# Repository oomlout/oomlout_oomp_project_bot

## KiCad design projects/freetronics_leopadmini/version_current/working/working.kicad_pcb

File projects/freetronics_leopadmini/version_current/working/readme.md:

# LEOPADMINI by freetronics  
This is a harvested standardized copy of a project from github.  
The original project can be found at:  
https://github.com/freetronics/LEOPADMINI  
Please consult that link for additional, details, files, and license information.  
Note: It was auto harvested and if the original repo had more than one board file or anything out of the ordinary the files here are likely not representative.

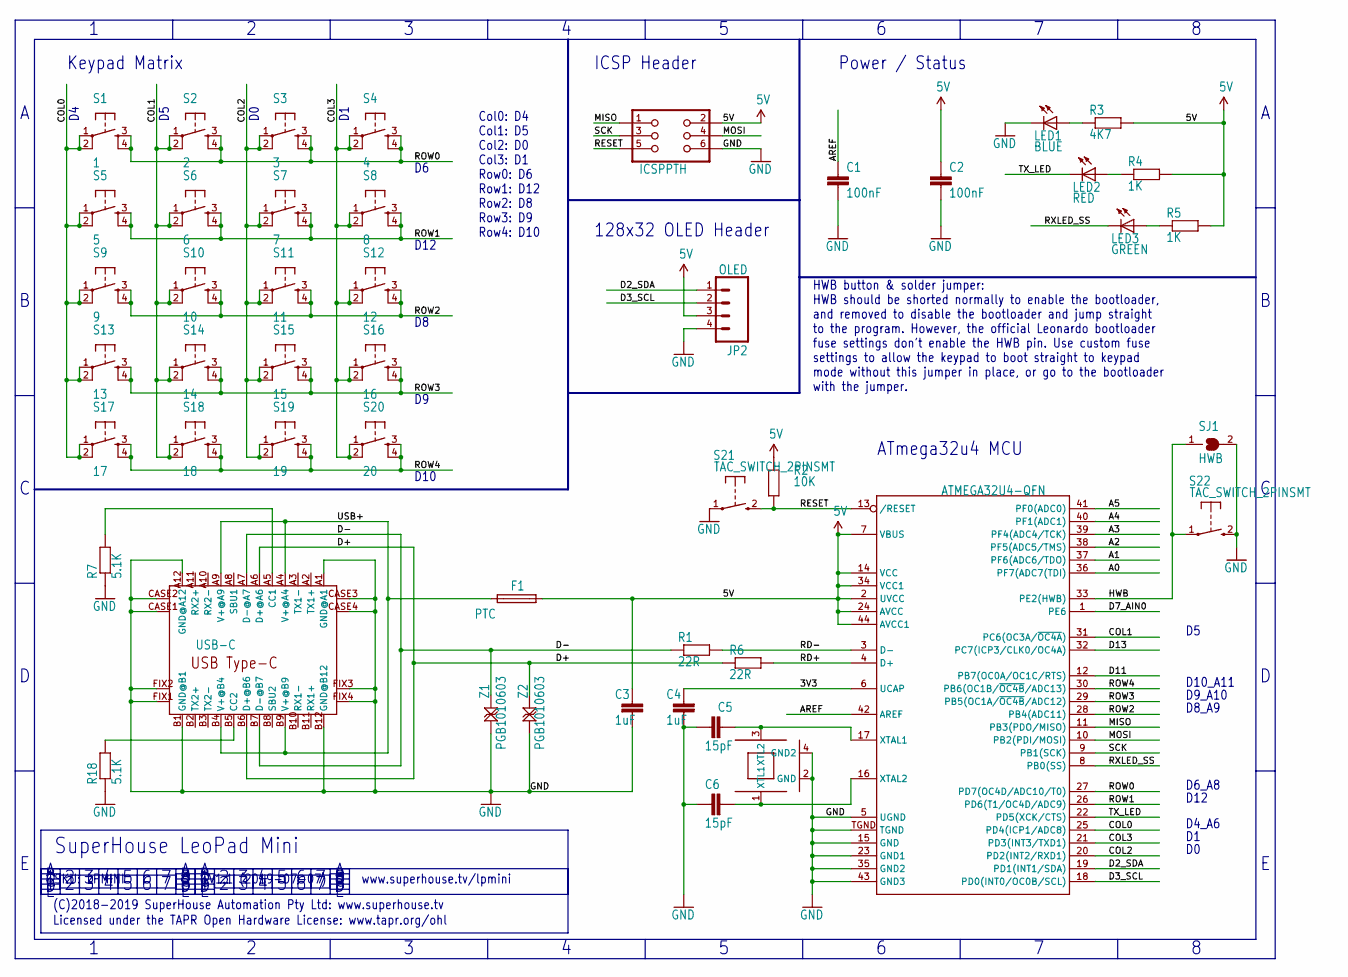
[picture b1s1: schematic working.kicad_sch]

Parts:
C1, C2: 100nF; C0603
C3, C4: 1uF; C0603
C5, C6: 15pF; C0603
F1: PTC; 1812
IC1: ATMEGA32U4-QFN; QFN-44N
ICSP0: ICSPPTH; 2X03PTH
JP2: OLED; 1X04
LED1: BLUE; LED-0603
LED2: RED; LED-0603
LED3: GREEN; LED-0603
R1, R6: 22R; R0603
R2: 10K; R0603
R3: 4K7; R0603
R4, R5: 1K; R0603
R7, R18: 5.1K; R0603
S1: 1; TACTILE-PTH-6MM
S2: 2; TACTILE-PTH-6MM
S3: 3; TACTILE-PTH-6MM
S4: 4; TACTILE-PTH-6MM
S5: 5; TACTILE-PTH-6MM
S6: 6; TACTILE-PTH-6MM
S7: 7; TACTILE-PTH-6MM
S8: 8; TACTILE-PTH-6MM
S9: 9; TACTILE-PTH-6MM
S10: 10; TACTILE-PTH-6MM
S11: 11; TACTILE-PTH-6MM
S12: 12; TACTILE-PTH-6MM
S13: 13; TACTILE-PTH-6MM
S14: 14; TACTILE-PTH-6MM
S15: 15; TACTILE-PTH-6MM
S16: 16; TACTILE-PTH-6MM
S17: 17; TACTILE-PTH-6MM
S18: 18; TACTILE-PTH-6MM
S19: 19; TACTILE-PTH-6MM
S20: 20; TACTILE-PTH-6MM
S21, S22: TAC_SWITCH_2PINSMT; TACTILE_SMD_3X4X2
SJ1: HWB; SJ
U$15: USB-C; USB-C-U52A
XTL1: CRYSTAL-GND3X2; CRYSTAL-SMD-3X2
Z1, Z2: PGB1010603; TVS0603

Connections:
3V3: C4.2, IC1.6 (UCAP)
5V: C2.1, C3.1, F1.2, IC1.2 (UVCC), IC1.7 (VBUS), IC1.14 (VCC), IC1.24 (AVCC), IC1.34 (VCC1), IC1.44 (AVCC1), ICSP0.2, JP2.3, R2.2, R3.2, R4.2, R5.2
A0: IC1.36 (PF7(ADC7(TDI))
A1: IC1.37 (PF6(ADC6/TDO))
A2: IC1.38 (PF5(ADC5/TMS))
A3: IC1.39 (PF4(ADC4/TCK))
A4: IC1.40 (PF1(ADC1))
A5: IC1.41 (PF0(ADC0))
AREF: C1.1, IC1.42 (AREF)
COL0: IC1.25 (PD4(ICP1/ADC8)), S1.1, S1.2, S5.1, S5.2, S9.1, S9.2, S13.1, S13.2, S17.1, S17.2
COL1: IC1.31 (PC6(OC3A/~OC4A)), S2.1, S2.2, S6.1, S6.2, S10.1, S10.2, S14.1, S14.2, S18.1, S18.2
COL2: IC1.20 (PD2(INT2/RXD1)), S3.1, S3.2, S7.1, S7.2, S11.1, S11.2, S15.1, S15.2, S19.1, S19.2
COL3: IC1.21 (PD3(INT3/TXD1)), S4.1, S4.2, S8.1, S8.2, S12.1, S12.2, S16.1, S16.2, S20.1, S20.2
D2_SDA: IC1.19 (PD1(INT1/SDA)), JP2.1
D3_SCL: IC1.18 (PD0(INT0/OC0B/SCL)), JP2.2
D7_AIN0: IC1.1 (PE6)
D11: IC1.12 (PB7(OC0A/OC1C/RTS))
D13: IC1.32 (PC7(ICP3/CLK0/OC4A))
D+: R6.1, U$15.A6 (D+@A6), U$15.B6 (D+@B6), Z2.2
D-: R1.1, U$15.A7 (D-@A7), U$15.B7 (D-@B7), Z1.2
GND: C1.2, C2.2, C3.2, C4.1, C5.1, C6.1, IC1.5 (UGND), IC1.15 (GND), IC1.23 (GND1), IC1.35 (GND2), IC1.43 (GND3), IC1.TGND, ICSP0.6, JP2.4, LED1.C, R7.1, R18.1, S21.1, S22.2 (S), SJ1.2, U$15.A1 (GND@A1), U$15.A12 (GND@A12), U$15.B1 (GND@B1), U$15.B12 (GND@B12), U$15.CASE1 (GND@CASE1), U$15.CASE2 (GND@CASE2), U$15.CASE3 (GND@CASE3), U$15.CASE4 (GND@CASE4), U$15.FIX1 (GND@FIX1), U$15.FIX2 (GND@FIX2), U$15.FIX3 (GND@FIX3), U$15.FIX4 (GND@FIX4), XTL1.2 (GND), XTL1.4 (GND2), Z1.1, Z2.1
HWB: IC1.33 (PE2(HWB)), S22.1, SJ1.1
MISO: IC1.11 (PB3(PDO/MISO)), ICSP0.1
MOSI: IC1.10 (PB2(PDI/MOSI)), ICSP0.4
unnamed: R18.2, U$15.B5 (CC2)
unnamed: LED1.A, R3.1
unnamed: LED2.A, R4.1
unnamed: LED3.A, R5.1
unnamed: C5.2, IC1.17 (XTAL1), XTL1.3 (XTL2)
unnamed: C6.2, IC1.16 (XTAL2), XTL1.1 (XTL1)
unnamed: R7.2, U$15.A5 (CC1)
RD+: IC1.4 (D+), R6.2
RD-: IC1.3 (D-), R1.2
RESET: IC1.13 (/RESET), ICSP0.5, R2.1, S21.2 (S)
ROW0: IC1.27 (PD7(OC4D/ADC10/T0)), S1.3, S1.4, S2.3, S2.4, S3.3, S3.4, S4.3, S4.4
ROW1: IC1.26 (PD6(T1/OC4D/ADC9)), S5.3, S5.4, S6.3, S6.4, S7.3, S7.4, S8.3, S8.4
ROW2: IC1.28 (PB4(ADC11)), S9.3, S9.4, S10.3, S10.4, S11.3, S11.4, S12.3, S12.4
ROW3: IC1.29 (PB5(OC1A/~OC4B/ADC12)), S13.3, S13.4, S14.3, S14.4, S15.3, S15.4, S16.3, S16.4
ROW4: IC1.30 (PB6(OC1B/~OC4B/ADC13)), S17.3, S17.4, S18.3, S18.4, S19.3, S19.4, S20.3, S20.4
RXLED_SS: IC1.8 (PB0(SS)), LED3.C
SCK: IC1.9 (PB1(SCK)), ICSP0.3
TX_LED: IC1.22 (PD5(XCK/CTS)), LED2.C
USB+: F1.1, U$15.A4 (V+@A4), U$15.A9 (V+@A9), U$15.B4 (V+@B4), U$15.B9 (V+@B9)

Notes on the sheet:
Col0: D4 Col1: D5 Col2: D0 Col3: D1 Row0: D6 Row1: D12 Row2: D8 Row3: D9 Row4: D10
D12
128x32 OLED Header
D9_A10
D6_A8
V1.1 (2019-07-07)
D10
(C)2018-2019 SuperHouse Automation Pty Ltd: www.superhouse.tv
Keypad Matrix
HWB button & solder jumper: HWB should be shorted normally to enable the bootloader, and removed to disable the bootloader and jump straight to the program. However, the official Leonardo bootloader fuse settings don't enable the HWB pin. Use custom fuse settings to allow the keypad to boot straigh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
Licensed under the TAPR Open Hardware License: www.tapr.org/ohl
D4_A6
SuperHouse LeoPad Mini
ICSP Header
Power / Status
D10_A11
SKU: LPMINI
D8_A9
www.superhouse.tv/lpmini
ATmega32u4 MCU

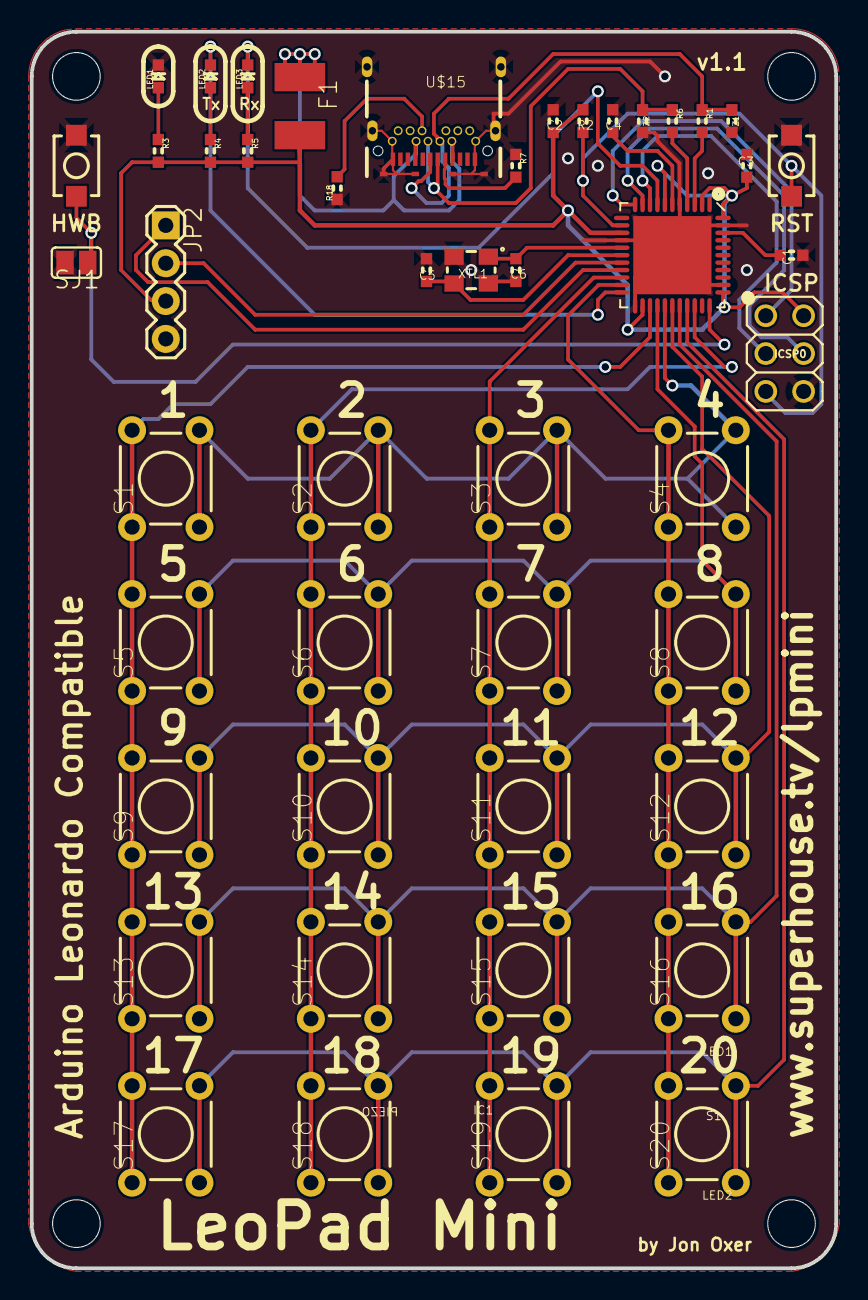
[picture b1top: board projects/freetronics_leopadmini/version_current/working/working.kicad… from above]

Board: 2 copper layers, 54.0 x 83.0 mm, 52 parts (0 on the bottom side), 34 nets.

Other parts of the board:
@HOLE0, @HOLE1, @HOLE2, @HOLE3: (no value)

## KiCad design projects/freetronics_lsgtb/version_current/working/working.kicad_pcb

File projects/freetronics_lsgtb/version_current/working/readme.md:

# LSGTB by freetronics  
This is a harvested standardized copy of a project from github.  
The original project can be found at:  
https://github.com/freetronics/LSGTB  
Please consult that link for additional, details, files, and license information.  
Note: It was auto harvested and if the original repo had more than one board file or anything out of the ordinary the files here are likely not representative.

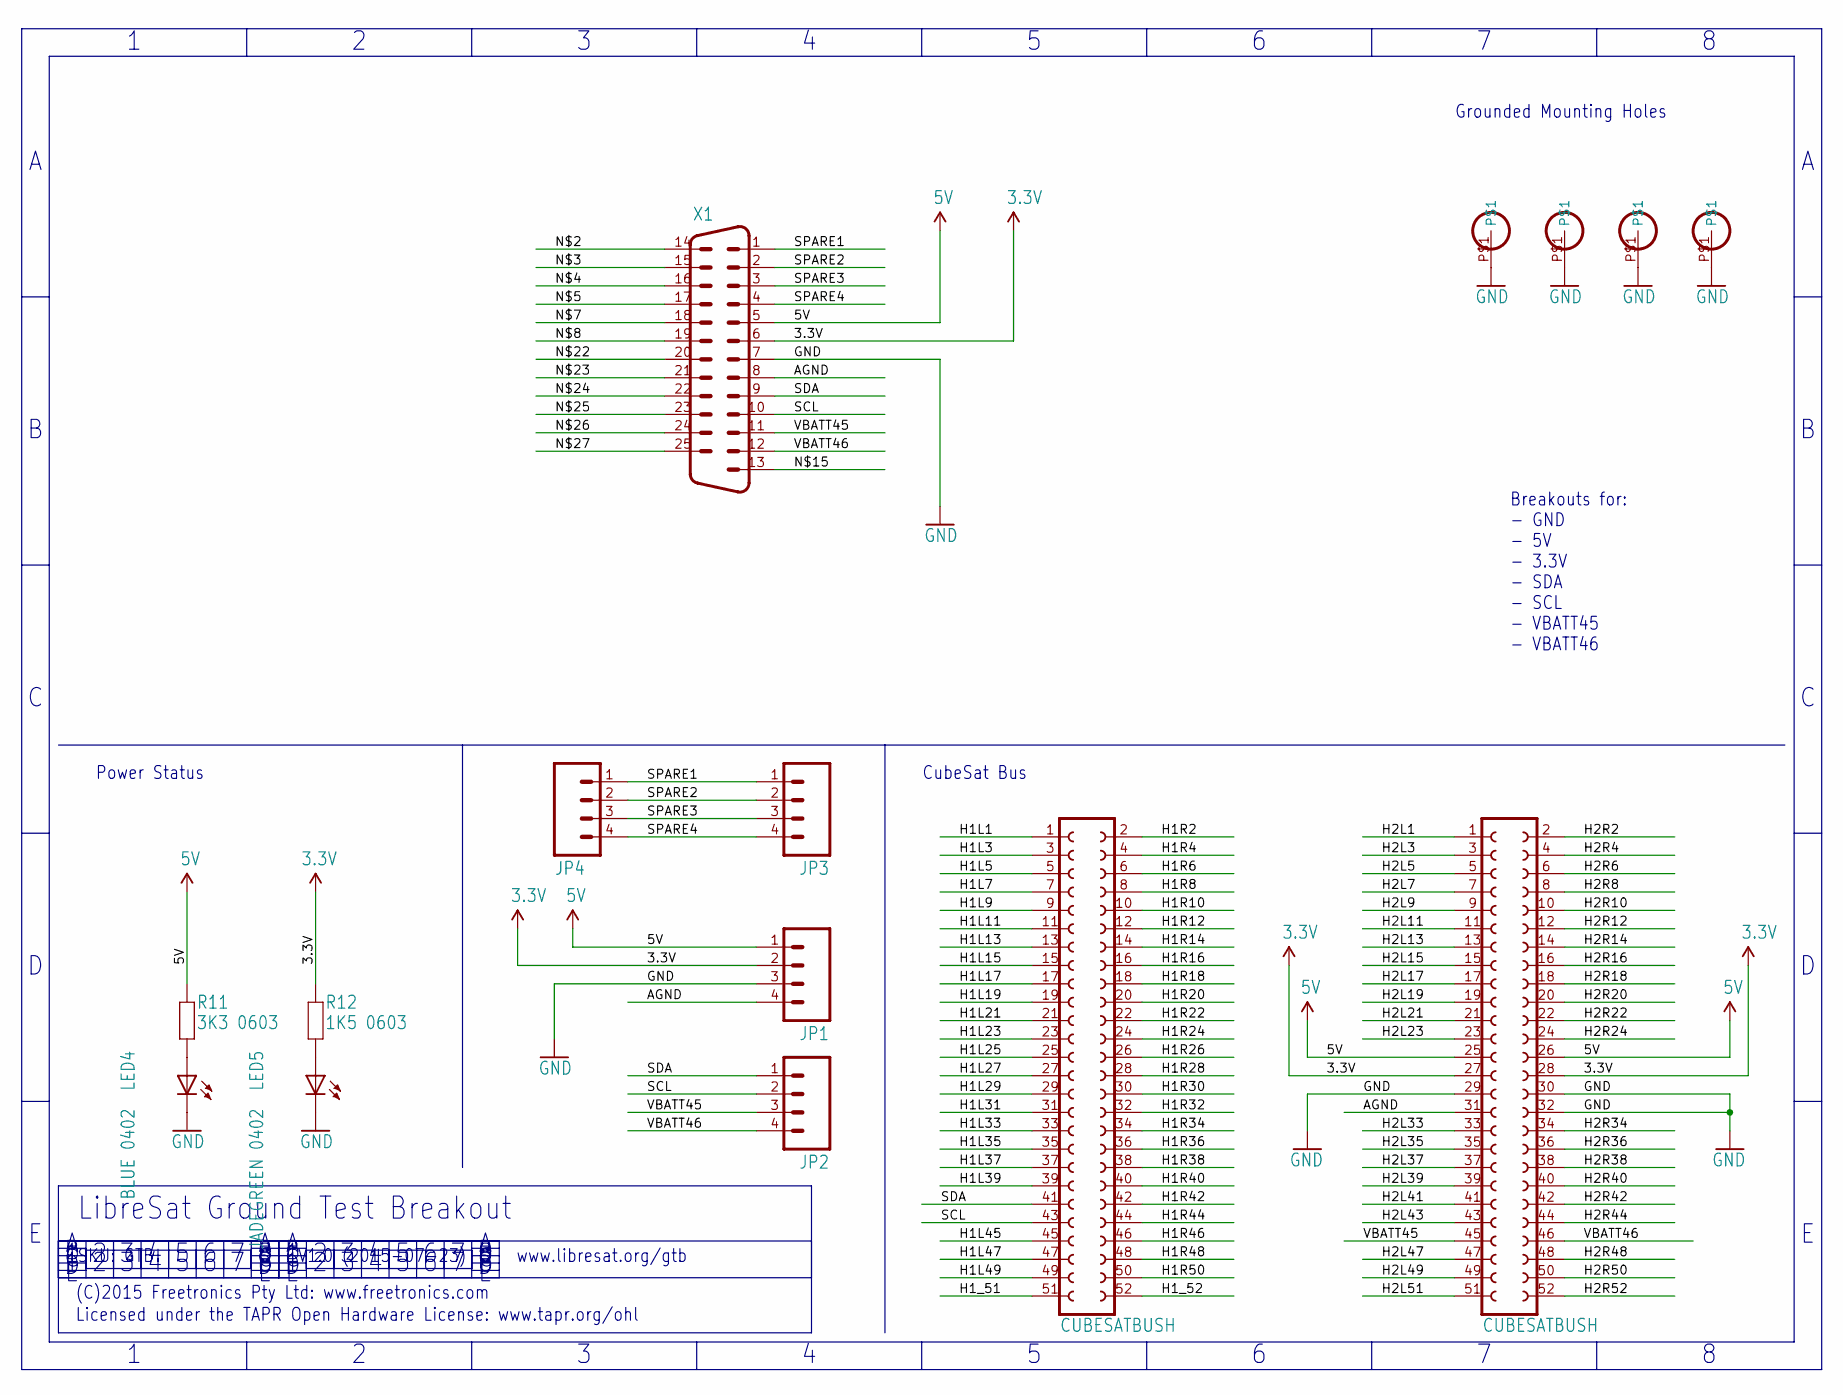
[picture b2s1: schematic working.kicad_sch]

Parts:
H1, H2: CUBESATBUSH; CUBESATBUS
JP1, JP2, JP3: M04SCREW; SCREWTERMINAL-3.5MM-4
JP4: M04PTH; 1X04
LED4: BLUE 0402; LED-0603
LED5: JADEGREEN 0402; LED-0603
MNT1, MNT2, MNT3, MNT4: HOLE3.2MM; HOLE32
R11: 3K3 0603; 0603
R12: 1K5 0603; 0603
X1: DB25HP; M25HP

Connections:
3.3V: H2.27, H2.28, JP1.2, R12.1, X1.6
5V: H2.25, H2.26, JP1.1, R11.1, X1.5
AGND: H2.31, JP1.4, X1.8
GND: H2.29, H2.30, H2.32, JP1.3, LED4.C, LED5.C, MNT1.P$1, MNT2.P$1, MNT3.P$1, MNT4.P$1, X1.7
H1L1: H1.1
H1L3: H1.3
H1L5: H1.5
H1L7: H1.7
H1L9: H1.9
H1L11: H1.11
H1L13: H1.13
H1L15: H1.15
H1L17: H1.17
H1L19: H1.19
H1L21: H1.21
H1L23: H1.23
H1L25: H1.25
H1L27: H1.27
H1L29: H1.29
H1L31: H1.31
H1L33: H1.33
H1L35: H1.35
H1L37: H1.37
H1L39: H1.39
H1L45: H1.45
H1L47: H1.47
H1L49: H1.49
H1R2: H1.2
H1R4: H1.4
H1R6: H1.6
H1R8: H1.8
H1R10: H1.10
H1R12: H1.12
H1R14: H1.14
H1R16: H1.16
H1R18: H1.18
H1R20: H1.20
H1R22: H1.22
H1R24: H1.24
H1R26: H1.26
H1R28: H1.28
H1R30: H1.30
H1R32: H1.32
H1R34: H1.34
H1R36: H1.36
H1R38: H1.38
H1R40: H1.40
H1R42: H1.42
H1R44: H1.44
H1R46: H1.46
H1R48: H1.48
H1R50: H1.50
H1_51: H1.51
H1_52: H1.52
H2L1: H2.1
H2L3: H2.3
H2L5: H2.5
H2L7: H2.7
H2L9: H2.9
H2L11: H2.11
H2L13: H2.13
H2L15: H2.15
H2L17: H2.17
H2L19: H2.19
H2L21: H2.21
H2L23: H2.23
H2L33: H2.33
H2L35: H2.35
H2L37: H2.37
H2L39: H2.39
H2L41: H2.41
H2L43: H2.43
H2L47: H2.47
H2L49: H2.49
H2L51: H2.51
H2R2: H2.2
H2R4: H2.4
H2R6: H2.6
H2R8: H2.8
H2R10: H2.10
H2R12: H2.12
H2R14: H2.14
H2R16: H2.16
H2R18: H2.18
H2R20: H2.20
H2R22: H2.22
H2R24: H2.24
H2R34: H2.34
H2R36: H2.36
H2R38: H2.38
H2R40: H2.40
H2R42: H2.42
H2R44: H2.44
H2R48: H2.48
H2R50: H2.50
H2R52: H2.52
unnamed: LED5.A, R12.2
unnamed: LED4.A, R11.2
SCL: H1.43, JP2.2, X1.10
SDA: H1.41, JP2.1, X1.9
SPARE1: JP3.1, JP4.1, X1.1
SPARE2: JP3.2, JP4.2, X1.2
SPARE3: JP3.3, JP4.3, X1.3
SPARE4: JP3.4, JP4.4, X1.4
VBATT45: H2.45, JP2.3, X1.11
VBATT46: H2.46, JP2.4, X1.12

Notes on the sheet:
(C)2015 Freetronics Pty Ltd: www.freetronics.com
V1.0 (2015-07-23)
Licensed under the TAPR Open Hardware License: www.tapr.org/ohl
Breakouts for: - GND - 5V - 3.3V - SDA - SCL - VBATT45 - VBATT46
Grounded Mounting Holes
CubeSat Bus
www.libresat.org/gtb
SKU: GTB
LibreSat Ground Test Breakout
Power Status

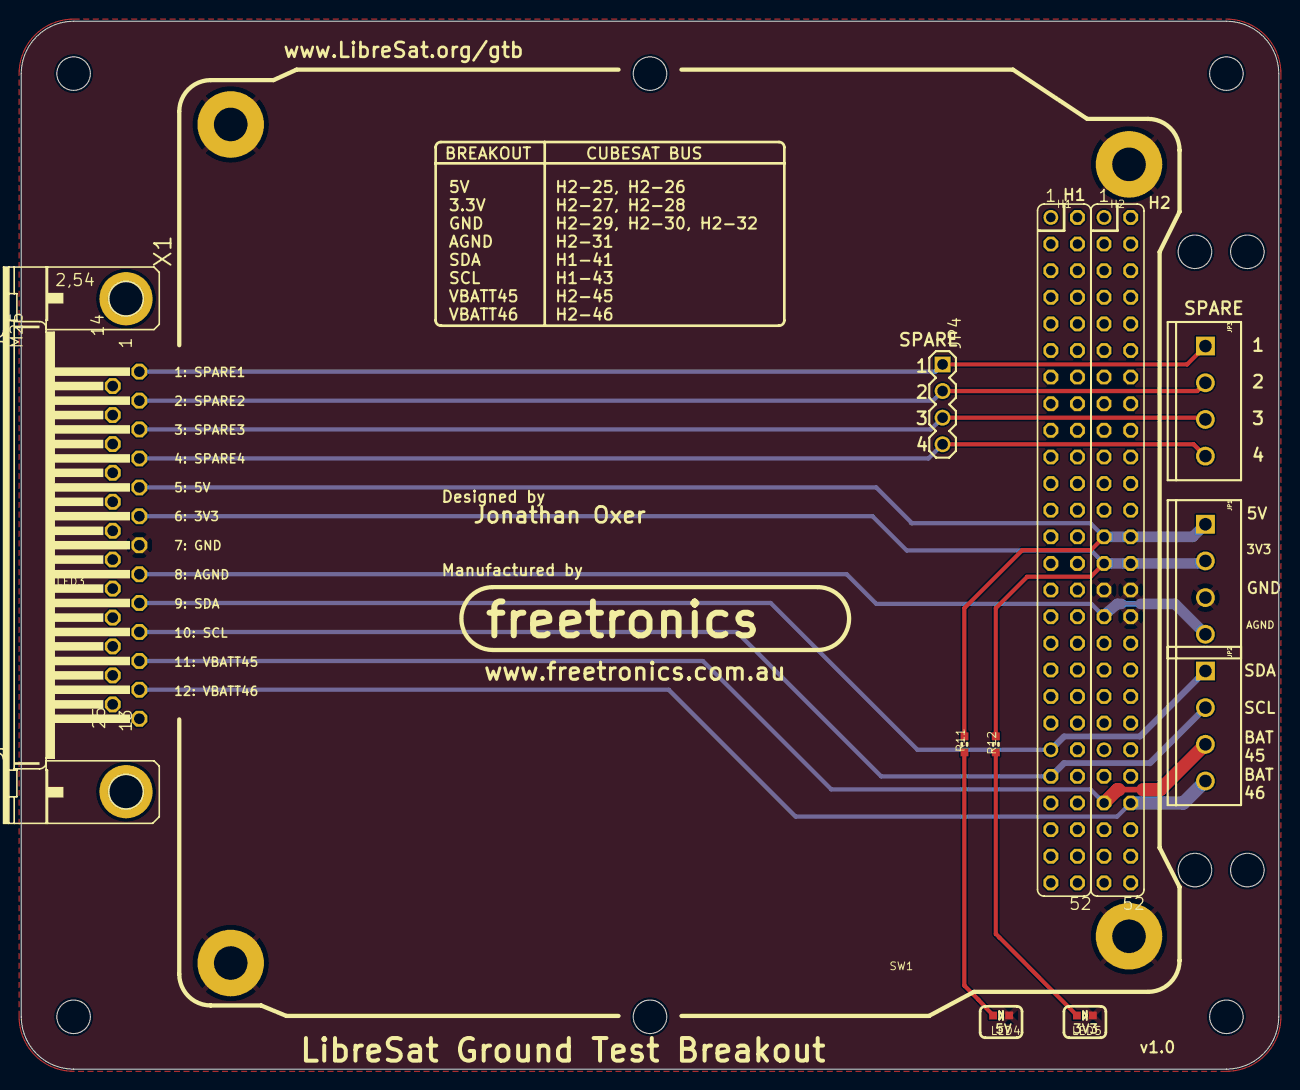
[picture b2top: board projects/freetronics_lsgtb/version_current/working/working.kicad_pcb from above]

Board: 2 copper layers, 120.0 x 100.0 mm, 26 parts (1 on the bottom side), 14 nets.

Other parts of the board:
@HOLE0, @HOLE1, @HOLE2, @HOLE3, @HOLE4, @HOLE5, @HOLE6, @HOLE7, @HOLE8, @HOLE9: (no value)
U$2: OSHW_10X200_NOTEXT

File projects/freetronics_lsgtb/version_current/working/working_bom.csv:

"Id";"Designator";"Footprint";"Quantity";"Designation";"Supplier and ref";
1;"@HOLE6,@HOLE5,@HOLE9,@HOLE0,@HOLE3,@HOLE7,@HOLE8,@HOLE1,@HOLE4,@HOLE2";"";10;"";;;
2;"JP3,JP2,JP1";"SCREWTERMINAL-3.5MM-4";3;"";;;
3;"LED4";"LED-0603";1;"BLUE 0402";;;
4;"H1,H2";"CUBESATBUS";2;"CUBESATBUSH";;;
5;"MNT3,MNT4,MNT2,MNT1";"HOLE32";4;"HOLE3.2MM";;;
6;"LED5";"LED-0603";1;"JADEGREEN 0402";;;
7;"R12";"0603";1;"1K5 0603";;;
8;"X1";"M25HP";1;"";;;
9;"JP4";"1X04";1;"";;;
10;"R11";"0603";1;"3K3 0603";;;
11;"U$2";"OSHW_10X200_NOTEXT";1;"";;;

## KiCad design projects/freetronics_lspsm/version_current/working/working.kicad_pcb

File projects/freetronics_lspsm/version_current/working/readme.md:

# LSPSM by freetronics  
This is a harvested standardized copy of a project from github.  
The original project can be found at:  
https://github.com/freetronics/LSPSM  
Please consult that link for additional, details, files, and license information.  
Note: It was auto harvested and if the original repo had more than one board file or anything out of the ordinary the files here are likely not representative.

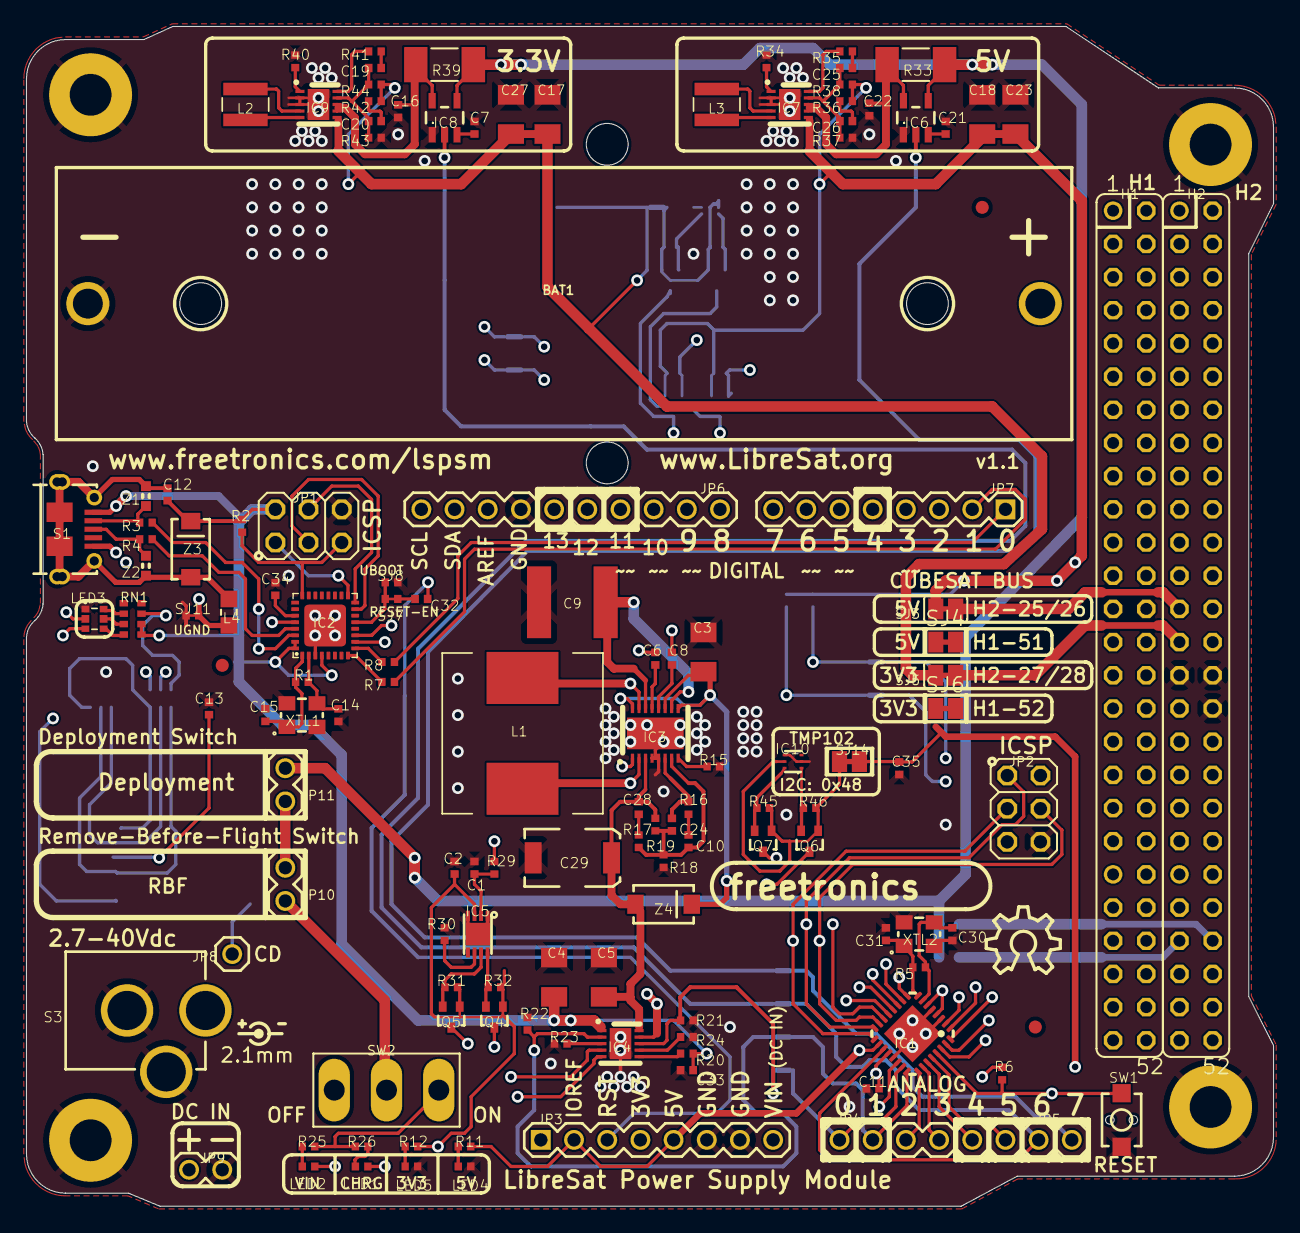
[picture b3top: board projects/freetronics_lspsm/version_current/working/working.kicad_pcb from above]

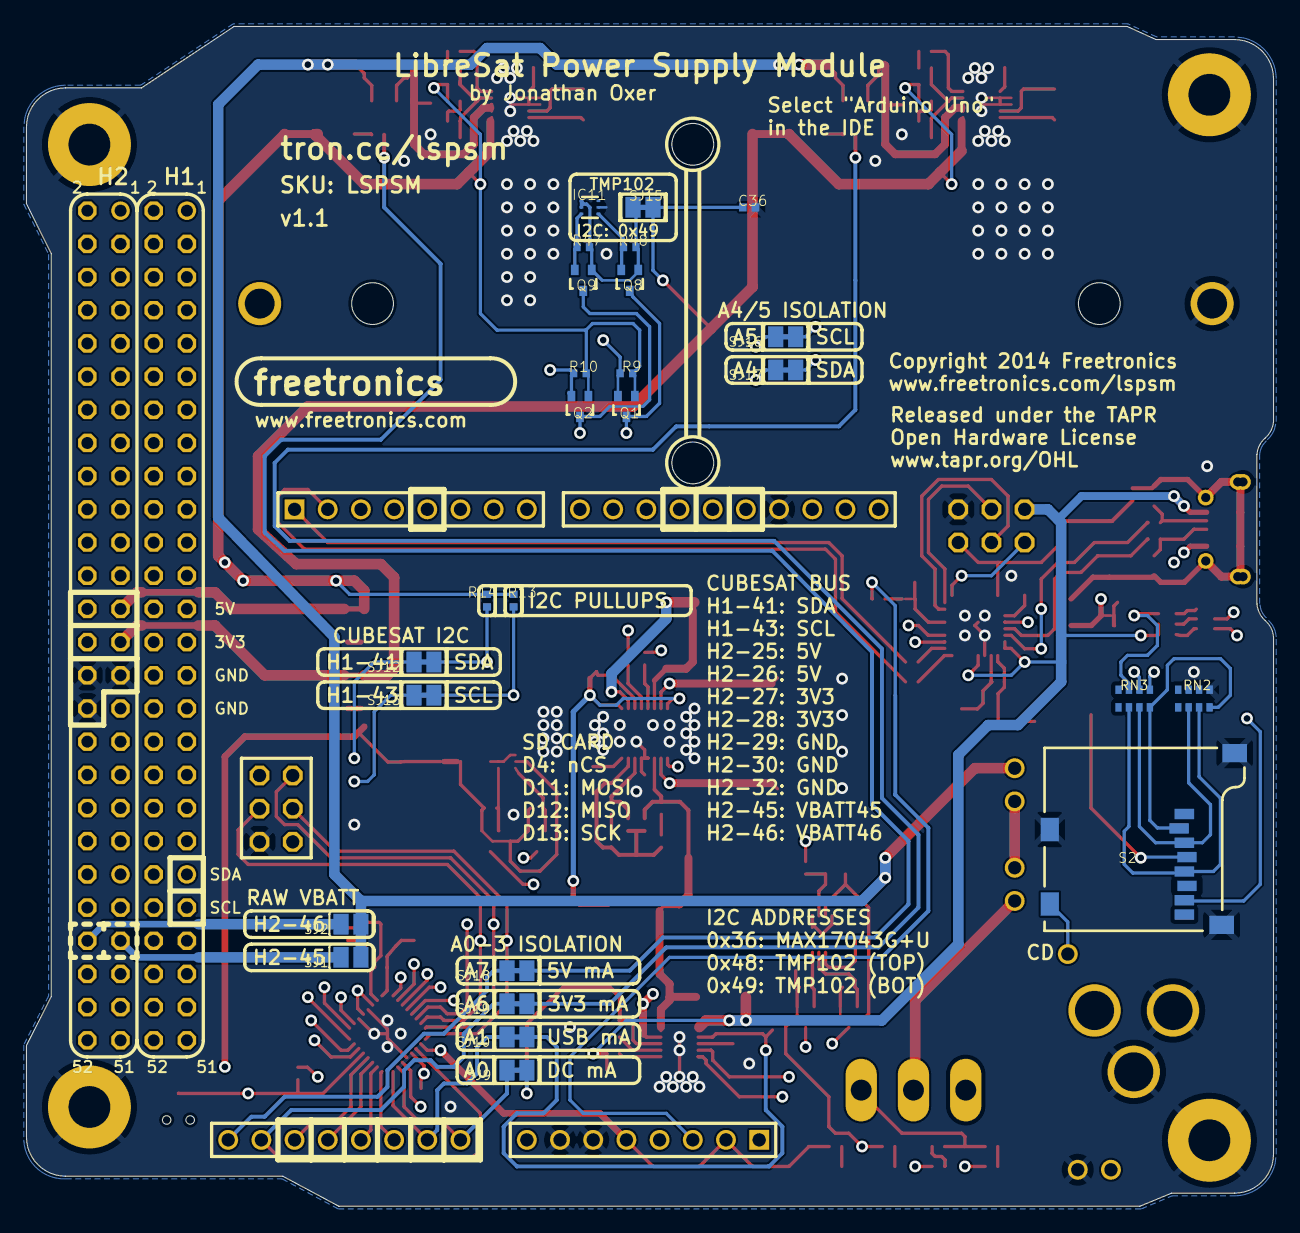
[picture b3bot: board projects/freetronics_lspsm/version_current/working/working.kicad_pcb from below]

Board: 4 copper layers, 95.5 x 90.3 mm, 167 parts (26 on the bottom side), 123 nets.

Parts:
@HOLE0, @HOLE1: (no value)
BAT1: CELLHOLDER-PCB; BH-18650-PC
C1: 1uF; 0402C
C2: 10nF 0402; 0402C
C3: 4.7uF TANTALUM; C1206K
C4, C5: 1uF TANTALUM; C1206K
C6, C7, C8, C11, C13, C21, C32, C33, C35, C36: 100nF 0402; 0402C
C9: 10uF Murata GRM55DR61H106K 2220; C2220K
C10: 3300pF 0402; 0402C
C12, C34: 1uF 0402; 0402C
C14, C15: 15pF 0402; 0402C
C16, C22: 10nF; 0402C
C17, C23: 100uF; C1206K
C18, C27: 47uF; C1206K
C19: 1nF 0402; 0402C
C20: 100pF; 0402C
C24: 27pF 0402; 0402C
C25: 1nF; 0402C
C26: 100pF 0402; 0402C
C28: 82pF 0402; 0402C
C29: 330uF 6.3V Sanyo TPB D3L; D3L
C30, C31: 22pF 0402; 0402C
FID1, FID2, FID3: FIDUCIAL1X2.5; FIDUCIAL-1X2.5
H1, H2: CUBESATBUSH; CUBESATBUS
IC1: ATmega328P; MLF32
IC2: ATMEGA16U2-MU; ATMEL_QFN32
IC3: LTC3115; DFN-16
IC4: LTC4078; DFN-10
IC5: MAX17043G+U; TDFN-8
IC6, IC8: MAX4372F; SOT23-5
IC7, IC9: LTC3536; DFN-10
IC10, IC11: TMP102; SOT563
JP1: ICSP:16U2; 2X03
JP2: ICSP:328P; 2X03
JP3, JP7: 1X08
JP4: 1X06
JP5, JP9, JP10, JP11: 1X02
JP6: M100.1; 1X10
JP8: CD; 1X01
L1: 33uH Coilcraft MSS1260-333ML; MSS1260
L2, L3: 4.7uH Coilcraft XFL4020; XFL4020
L4: 0805 INDUCTOR; 0805-LARGE
LED1: RED 0402; LED-0402
LED2, LED4: BLUE 0402; LED-0402
LED3: RGBLEDSMT; 19-337
LED5: JADEGREEN 0402; LED-0402
MNT1, MNT2, MNT3, MNT4: HOLE3.2MM; HOLE32
Q1, Q2, Q4, Q5, Q6, Q7, Q8, Q9: RJU003N03 N-MOSFET; SOT32-3
R1, R5: 1M 0402; 0402
R2, R6, R9, R10, R24, R31, R32, R45, R46, R47, R48: 10K 0402; 0402
R3, R4: 22R; 0402
R7, R8, R29: 1K 0402; 0402
R11, R25: 3K3 0402; 0402
R12, R26: 1K5 0402; 0402
R13, R14, R30: 4K7 0402; 0402
R15: 121K 1% 0402; 0402
R16: 93.1K 1% 0402; 0402
R17: 1M 1% 0402; 0402
R18, R19: 249K 1% 0402; 0402
R20: 1K; 0402
R21, R22, R23: 1K 1% 0402; 0402
R33, R39: 0.1R 2010; R2010
R34, R40: 100K; 0402
R35: 49.9K; 0402
R36: 15K 0402; 0402
R37: 115K 1% 0402; 0402
R38, R44: 845K 1% 0402; 0402
R41: 49.9K 1% 0402; 0402
R42: 15K; 0402
R43: 187K 1% 0402; 0402
RN1: 1K5; CAY16
RN2: 2K2; CAY16
RN3: 1K; CAY16
S1: USB-6PSMT; USB-MICROB-MB05PMXX
S2: microSD; MICRO-SD-SOCKET-PP
S3: POWER_JACKPTH; POWER_JACK_PTH
SJ1: VBATT45; SJ
SJ2: VBATT46; SJ
SJ3: 5V_EN; SJC
SJ4, SJ6, SJ12, SJ13, SJ14, SJ15, SJ16, SJ17, SJ18, SJ19: SJCN; SJC
SJ5: 3V3_EN; SJC
SJ7: RESET-EN; 0402SJC
SJ8: UBOOT; 0402SJO
SJ9: DC_I; SJC
SJ10: USB_I; SJC
SJ11: UGND; 0402SJC
SW1: RESET; TACTILE_SWITCH_SMD_2PIN_TINY
SW2: SWITCH-SPDT; SS-12F100
U$2: OSHW_10X200_NOTEXT
XTL1, XTL2: 16MHz; CRYSTAL-SMD-3X2
Z1, Z2: PGB1010603; 0603
Z3: 5.6V 1W Zener; SMA-DIODE
Z4: 50V 1W Zener; SMA-DIODE

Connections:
3.3V: C2.1, C13.1, C17.2, C27.2, C35.1, C36.1, IC5.3, IC9.6, JP3.4, Q4.1, Q5.1, R12.1, R31.2, R32.2, R42.2, R44.2, S2.4, SJ5.1, SJ6.1, SJ14.1, SJ15.1
3V3SENSED: C16.1, IC8.5, IC9.7, IC9.8, R39.2
5V: C7.1, C18.2, C21.1, C23.2, IC1.4, IC1.6, IC1.18, IC6.3, IC7.6, IC8.3, JP2.2, JP3.2, JP3.5, Q1.1, Q2.1, R6.2, R9.2, R10.2, R11.1, R13.2, R14.2, R36.2, R38.2, SJ3.1, SJ4.1
5VSENSED: C22.1, IC6.5, IC7.7, IC7.8, R33.2
+5V_SYS_25: H2.25, SJ3.2
+5V_SYS_26: H2.26, SJ4.2
A0: IC1.23, JP4.1, SJ9.2
A1: IC1.24, JP4.2, SJ10.2
A2: IC1.25, JP4.3
A3: IC1.26, JP4.4
A4_SDA: IC1.27, JP4.5, JP6.9, SJ17.1
A5_SCL: IC1.28, JP4.6, JP6.10, SJ16.1
A6: IC1.19, JP5.1, SJ19.2
A7: IC1.22, JP5.2, SJ18.2
AREF: C11.1, IC1.20, JP6.8
BAT: BAT1.+, IC4.9, R25.1, R26.1, R29.2, SW2.1
CELL: C1.1, IC5.2, R29.1
D0_RX: IC1.30, JP7.1, R8.1
D1_TX: IC1.31, JP7.2, R7.1
D2: IC1.32, JP7.3
D3: IC1.1, JP7.4
D4: IC1.2, JP7.5, RN3.5
D5: IC1.9, JP7.6
D6: IC1.10, JP7.7
D7: IC1.11, JP7.8
D8: IC1.12, JP6.1
D9: IC1.13, JP6.2
D10: IC1.14, JP6.3
D11_MOSI: IC1.15, JP2.4, JP6.4, RN3.6
D12_MISO: IC1.16, JP2.1, JP6.5, S2.7
D13_SCK: IC1.17, JP2.3, JP6.6, RN1.3, RN3.7
D+: R4.1, S1.D+, Z2.2
D-: R3.1, S1.D-, Z1.2
DC_I: IC4.8, R21.1, SJ9.1
DTR: IC2.13, SJ7.1, SJ8.2
GND: BAT1.-, C1.2, C2.2, C3.1, C4.1, C5.1, C7.2, C9.1, C11.2, C13.2, C14.1, C15.1, C16.2, C17.1, C18.1, C21.2, C22.2, C23.1, C27.1, C29.NEG, C30.1, C31.1, C33.2, C34.2, C35.2, C36.2, H2.29, H2.30, H2.32, IC1.3, IC1.5, IC1.21, IC1.TGND, IC2.3, IC2.EXP, IC3.4, IC3.5, IC3.TGND, IC4.TGND, IC5.1, IC5.4, IC5.EP, IC6.1, IC7.2, IC7.3, IC7.TGND, IC8.1, IC9.2, IC9.3, IC9.TGND, IC10.2, IC10.4, IC11.2, JP1.6, JP2.6, JP3.6, JP3.7, JP6.7, JP9.1, LED3.1, LED4.C, LED5.C, MNT1.P$1, MNT2.P$1, MNT3.P$1, MNT4.P$1, R15.1, R18.1, R21.2, R22.2, R23.2, R24.2, R30.1, R34.2, R37.2, R40.2, R43.2, RN2.1, RN2.2, RN2.3, S2.6, S2.CD2, S2.GND1, S2.GND2, S3.GND, S3.GNDBREAK, SJ8.1, SJ11.2, SW1.1, XTL1.2, XTL1.4, XTL2.2, XTL2.4
MISO2: IC2.17, JP1.1
MOSI2: IC2.16, JP1.4
unnamed: LED5.A, R12.2
unnamed: JP10.2, JP11.1
unnamed: LED2.A, R25.2
unnamed: JP10.1, SW2.2
unnamed: LED4.A, R11.2
unnamed: IC5.8, Q4.2, R32.1
unnamed: IC5.7, Q5.2, R31.1
unnamed: C30.2, IC1.7, R5.2, XTL2.3
unnamed: IC6.2, SJ18.1
unnamed: C15.2, IC2.1, R1.1, XTL1.1
unnamed: RN2.8, RN3.4, S2.2
unnamed: LED3.4, RN1.6
unnamed: IC9.10, R41.1
unnamed: LED3.5, RN1.7
unnamed: LED3.6, RN1.8
unnamed: IC9.4, L2.1
unnamed: IC9.5, L2.2
unnamed: IC4.7, R24.1
unnamed: IC9.1, R40.1
unnamed: IC7.4, L3.1
unnamed: C19.1, R41.2
unnamed: C31.2, IC1.8, R5.1, XTL2.1
unnamed: C20.2, R42.1
unnamed: C19.2, C20.1, IC9.9, R43.1, R44.1
unnamed: IC4.4, LED2.C
unnamed: IC7.5, L3.2
unnamed: IC7.1, R34.1
unnamed: C25.1, R35.2
unnamed: IC7.10, R35.1
unnamed: C26.2, R36.1
unnamed: C25.2, C26.1, IC7.9, R37.1, R38.1
unnamed: C34.1, IC2.27
unnamed: IC4.3, R23.1
unnamed: IC4.6, R20.2
unnamed: C10.1, R16.2
unnamed: C12.2, L4.2, S1.FIX1, S1.FIX2, S1.PIN1, S1.PIN2, S1.TAB1, S1.TAB2, Z1.1, Z2.1, Z3.A
unnamed: C3.2, IC3.9, IC3.11, IC3.16, Z4.C
unnamed: C6.2, IC3.13
unnamed: C8.2, IC3.12
unnamed: C6.1, IC3.15, L1.1
unnamed: C8.1, IC3.2, L1.2
unnamed: C24.1, IC3.6, R16.1
unnamed: C10.2, C24.2, IC3.7, R17.1, R18.2, R19.1
unnamed: RN2.6, RN3.3, S2.3
unnamed: IC3.8, R15.2
unnamed: RN2.7, RN3.2, S2.5
unnamed: C28.2, R19.2
unnamed: JP8.1, S2.CD1
unnamed: IC8.2, SJ19.1
unnamed: C14.2, IC2.2, R1.2, XTL1.3
unnamed: IC10.5, Q6.1, Q7.1, R45.2, R46.2, SJ14.2
unnamed: IC11.4, IC11.5, Q8.1, Q9.1, R47.2, R48.2, SJ15.2
unnamed: Q1.2, R9.1, SJ16.2
unnamed: IC2.28, L4.1, S1.GND, SJ11.1
unnamed: Q2.2, R10.1, SJ17.2
unnamed: C32.1, SJ7.2
unnamed: LED1.A, R26.2
unnamed: IC4.5, LED1.C
unnamed: IC10.1, Q6.2, R46.1
unnamed: IC10.6, Q7.2, R45.1
unnamed: IC11.6, Q9.2, R47.1
unnamed: IC11.1, Q8.2, R48.1
PVIN: C9.2, IC3.1, IC3.10, IC3.14, JP3.8, JP9.2, S3.PWR
PVOUT: C5.2, C28.1, C29.POS, IC3.3, IC4.10, R17.2, Z4.A
QST: IC5.6, R30.2
RD+: IC2.29, R4.2
RD-: IC2.30, R3.2
RESET: C32.2, IC1.29, JP2.5, JP3.3, R6.1, SW1.2
RESET2: IC2.24, JP1.5, R2.1
RXLED: IC2.10, LED3.3
SCK2: IC2.15, JP1.3
SCL: Q1.3, Q5.3, Q6.3, Q8.3, R13.1, SJ13.1
SDA: Q2.3, Q4.3, Q7.3, Q9.3, R14.1, SJ12.1
SYS_SCL: H1.43, SJ13.2
SYS_SDA: H1.41, SJ12.2
TXLED: IC2.11, LED3.2
USBRXD: IC2.9, R8.2
USBTXD: IC2.8, R7.2
USBVCC: C4.2, C12.1, C33.1, IC2.4, IC2.31, IC2.32, IC4.1, JP1.2, R2.2, R20.1, RN1.1, RN1.2, S1.VBUS, Z3.C
USB_I: IC4.2, R22.1, SJ10.1
VBATT: IC6.4, IC8.4, JP11.2, R33.1, R39.1, SJ1.1, SJ2.1
VBATT45: H2.45, SJ1.2
VBATT46: H2.46, SJ2.2
VCC_SYS_27: H2.27, SJ5.2
VCC_SYS_28: H2.28, SJ6.2

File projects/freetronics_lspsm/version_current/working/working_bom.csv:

"Id";"Designator";"Footprint";"Quantity";"Designation";"Supplier and ref";
1;"IC9,IC7";"DFN-10";2;"LTC3536";;;
2;"C6,C13,C32,C33,C21,C7,C35,C8,C11,C36";"0402C";10;"100nF 0402";;;
3;"C18,C27";"C1206K";2;"47uF";;;
4;"JP3,JP7";"1X08";2;"";;;
5;"R44,R38";"0402";2;"845K 1% 0402";;;
6;"L3,L2";"XFL4020";2;"4.7uH Coilcraft XFL4020";;;
7;"R12,R26";"0402";2;"1K5 0402";;;
8;"C1";"0402C";1;"1uF";;;
9;"R42";"0402";1;"15K";;;
10;"JP5,JP11,JP10,JP9";"1X02";4;"";;;
11;"Q5,Q7,Q6,Q4,Q8,Q1,Q2,Q9";"SOT32-3";8;"RJU003N03 N-MOSFET";;;
12;"R17";"0402";1;"1M 1% 0402";;;
13;"IC10,IC11";"SOT563";2;"TMP102";;;
14;"C26";"0402C";1;"100pF 0402";;;
15;"Z4";"SMA-DIODE";1;"50V 1W Zener";;;
16;"R33,R39";"R2010";2;"0.1R 2010";;;
17;"IC1";"MLF32";1;"ATmega328P";;;
18;"R6,R46,R32,R45,R2,R24,R31,R9,R47,R10,R48";"0402";11;"10K 0402";;;
19;"C14,C15";"0402C";2;"15pF 0402";;;
20;"R15";"0402";1;"121K 1% 0402";;;
21;"C16,C22";"0402C";2;"10nF";;;
22;"SJ5";"SJC";1;"3V3_EN";;;
23;"R23,R22,R21";"0402";3;"1K 1% 0402";;;
24;"C30,C31";"0402C";2;"22pF 0402";;;
25;"JP8";"1X01";1;"CD";;;
26;"R8,R29,R7";"0402";3;"1K 0402";;;
27;"SJ3";"SJC";1;"5V_EN";;;
28;"R43";"0402";1;"187K 1% 0402";;;
29;"R41";"0402";1;"49.9K 1% 0402";;;
30;"IC8,IC6";"SOT23-5";2;"MAX4372F";;;
31;"R34,R40";"0402";2;"100K";;;
32;"Z2,Z1";"0603";2;"PGB1010603";;;
33;"L4";"0805-LARGE";1;"0805 INDUCTOR";;;
34;"MNT3,MNT4,MNT2,MNT1";"HOLE32";4;"HOLE3.2MM";;;
35;"FID2,FID1,FID3";"FIDUCIAL-1X2.5";3;"FIDUCIAL1X2.5";;;
36;"IC4";"DFN-10";1;"LTC4078";;;
37;"C34,C12";"0402C";2;"1uF 0402";;;
38;"R36";"0402";1;"15K 0402";;;
39;"R37";"0402";1;"115K 1% 0402";;;
40;"R16";"0402";1;"93.1K 1% 0402";;;
41;"SW1";"TACTILE_SWITCH_SMD_2PIN_TINY";1;"RESET";;;
42;"R30,R14,R13";"0402";3;"4K7 0402";;;
43;"JP4";"1X06";1;"";;;
44;"XTL2,XTL1";"CRYSTAL-SMD-3X2";2;"16MHz";;;
45;"C10";"0402C";1;"3300pF 0402";;;
46;"R11,R25";"0402";2;"3K3 0402";;;
47;"C9";"C2220K";1;"10uF Murata GRM55DR61H106K 2220";;;
48;"R19,R18";"0402";2;"249K 1% 0402";;;
49;"LED5";"LED-0402";1;"JADEGREEN 0402";;;
50;"H1,H2";"CUBESATBUS";2;"CUBESATBUSH";;;
51;"C2";"0402C";1;"10nF 0402";;;
52;"SJ7";"0402SJC";1;"RESET-EN";;;
53;"SJ11";"0402SJC";1;"UGND";;;
54;"C24";"0402C";1;"27pF 0402";;;
55;"R4,R3";"0402";2;"22R";;;
56;"LED4,LED2";"LED-0402";2;"BLUE 0402";;;
57;"C4,C5";"C1206K";2;"1uF TANTALUM";;;
58;"R1,R5";"0402";2;"1M 0402";;;
59;"C3";"C1206K";1;"4.7uF TANTALUM";;;
60;"R35";"0402";1;"49.9K";;;
61;"S3";"POWER_JACK_PTH";1;"POWER_JACKPTH";;;
62;"C20";"0402C";1;"100pF";;;
63;"IC2";"ATMEL_QFN32";1;"ATMEGA16U2-MU";;;
64;"R20";"0402";1;"1K";;;
65;"LED3";"19-337";1;"RGBLEDSMT";;;
66;"C25";"0402C";1;"1nF";;;
67;"IC5";"TDFN-8";1;"MAX17043G+U";;;
68;"@HOLE1,@HOLE0";"";2;"";;;
69;"C17,C23";"C1206K";2;"100uF";;;
70;"JP2";"2X03";1;"ICSP:328P";;;
71;"Z3";"SMA-DIODE";1;"5.6V 1W Zener";;;
72;"SW2";"SS-12F100";1;"SWITCH-SPDT";;;
73;"SJ6,SJ14,SJ4,SJ15,SJ19,SJ18,SJ16,SJ13,SJ12,SJ17";"SJC";10;"SJCN";;;
74;"BAT1";"BH-18650-PC";1;"CELLHOLDER-PCB";;;
75;"IC3";"DFN-16";1;"LTC3115";;;
76;"C19";"0402C";1;"1nF 0402";;;
77;"C28";"0402C";1;"82pF 0402";;;
78;"JP6";"1X10";1;"M100.1";;;
79;"LED1";"LED-0402";1;"RED 0402";;;
80;"SJ8";"0402SJO";1;"UBOOT";;;
81;"L1";"MSS1260";1;"33uH Coilcraft MSS1260-333ML";;;
82;"S1";"USB-MICROB-MB05PMXX";1;"USB-6PSMT";;;
83;"C29";"D3L";1;"330uF 6.3V Sanyo TPB D3L";;;
84;"RN1";"CAY16";1;"1K5";;;
85;"U$2";"OSHW_10X200_NOTEXT";1;"";;;
86;"JP1";"2X03";1;"ICSP:16U2";;;
87;"RN3";"CAY16";1;"1K";;;
88;"SJ1";"SJ";1;"VBATT45";;;
89;"S2";"MICRO-SD-SOCKET-PP";1;"microSD";;;
90;"SJ2";"SJ";1;"VBATT46";;;
91;"RN2";"CAY16";1;"2K2";;;
92;"SJ9";"SJC";1;"DC_I";;;
93;"SJ10";"SJC";1;"USB_I";;;

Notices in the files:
projects/freetronics_leopadmini/version_current/working/working.kicad_pcb:
Copyright 2018 SuperHouse Automation Pty Ltd
projects/freetronics_leopadretrofit/version_current/working/working.kicad_sch:
(C)2018 Freetronics Pty Ltd: www.freetronics.com
projects/freetronics_lsgtb/version_current/working/working.kicad_pcb:
Copyright 2015 Freetronics
projects/freetronics_lspsm/version_current/working/working.kicad_pcb:
Copyright 2014 Freetronics
projects/freetronics_lssm/version_current/working/working.kicad_pcb:
Copyright 2013 Freetronics Pty Ltd
Open Hardware Licence
